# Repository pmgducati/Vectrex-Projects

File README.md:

# Vectrex-Projects
I created a few things for my Vectrex:

I have included the Gerber files for the PCBs in the controller and STLs of all the 3D printed parts. (the Eagle PCBs and Solidworks CAD Models are also inlcuded). Feel free to use my designs for yourself and modifiy them as you see fit.  

The designs are for personal use and may not be used for commericial use.

  1. A analog controller with a x-Axis sterring wheel, exposed center adjustment, headphone jack for foot pedal controls and a toggle to change what button the footpedal triggers.

  2. A bezel to work with Blacklighter's UV reactive overalys

  3. A shell for Vectrexer's VecMulti Cart

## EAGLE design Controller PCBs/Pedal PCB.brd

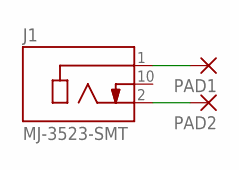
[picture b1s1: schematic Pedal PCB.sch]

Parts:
J1: MJ-3523-SMT; CUI_MJ-3523-SMT
PAD1, PAD2: SMD2; SMD1,27-2,54

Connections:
unnamed: J1.1, PAD1.1
unnamed: J1.2, PAD2.1

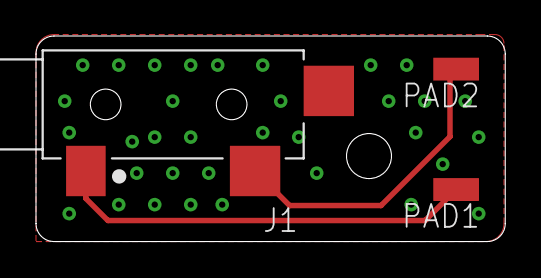
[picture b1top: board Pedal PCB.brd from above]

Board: 2 copper layers, 26.1 x 11.4 mm, 3 parts (0 on the bottom side), 2 nets.

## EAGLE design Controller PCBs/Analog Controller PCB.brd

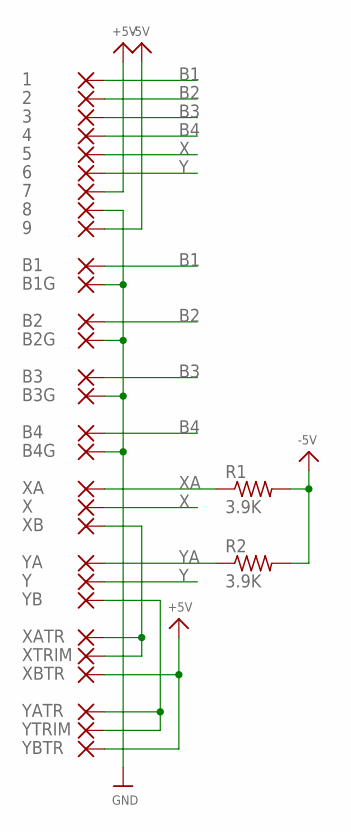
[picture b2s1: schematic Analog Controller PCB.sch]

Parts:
1, 2, 3, 4, 5, 6, 7, 8, 9: SMD2; SMD1,27-2,54
B1, B1G, B2, B2G, B3, B3G, B4, B4G: SMD2; SMD1,27-2,54
R1, R2: 3.9K; R1206
X: SMD2; SMD1,27-2,54
XA: SMD2; SMD1,27-2,54
XATR: SMD2; SMD1,27-2,54
XB: SMD2; SMD1,27-2,54
XBTR: SMD2; SMD1,27-2,54
XTRIM: SMD2; SMD1,27-2,54
Y: SMD2; SMD1,27-2,54
YA: SMD2; SMD1,27-2,54
YATR: SMD2; SMD1,27-2,54
YB: SMD2; SMD1,27-2,54
YBTR: SMD2; SMD1,27-2,54
YTRIM: SMD2; SMD1,27-2,54

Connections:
+5V: 7.1, XBTR.1, YBTR.1
-5V: 9.1, R1.2, R2.2
B1: 1.1, B1.1
B2: 2.1, B2.1
B3: 3.1, B3.1
B4: 4.1, B4.1
GND: 8.1, B1G.1, B2G.1, B3G.1, B4G.1
X: 5.1, X.1
XA: R1.1, XA.1
XB: XATR.1, XB.1, XTRIM.1
Y: 6.1, Y.1
YA: R2.1, YA.1
YB: YATR.1, YB.1, YTRIM.1

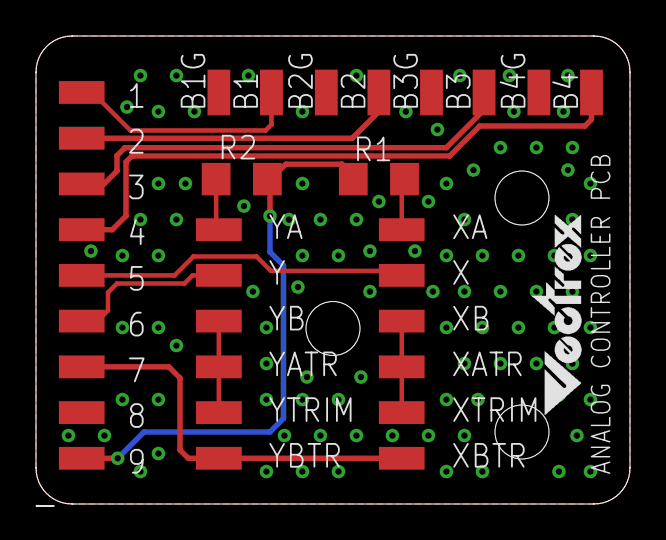
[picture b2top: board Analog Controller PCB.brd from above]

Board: 2 copper layers, 33.0 x 26.0 mm, 31 parts (0 on the bottom side), 13 nets.

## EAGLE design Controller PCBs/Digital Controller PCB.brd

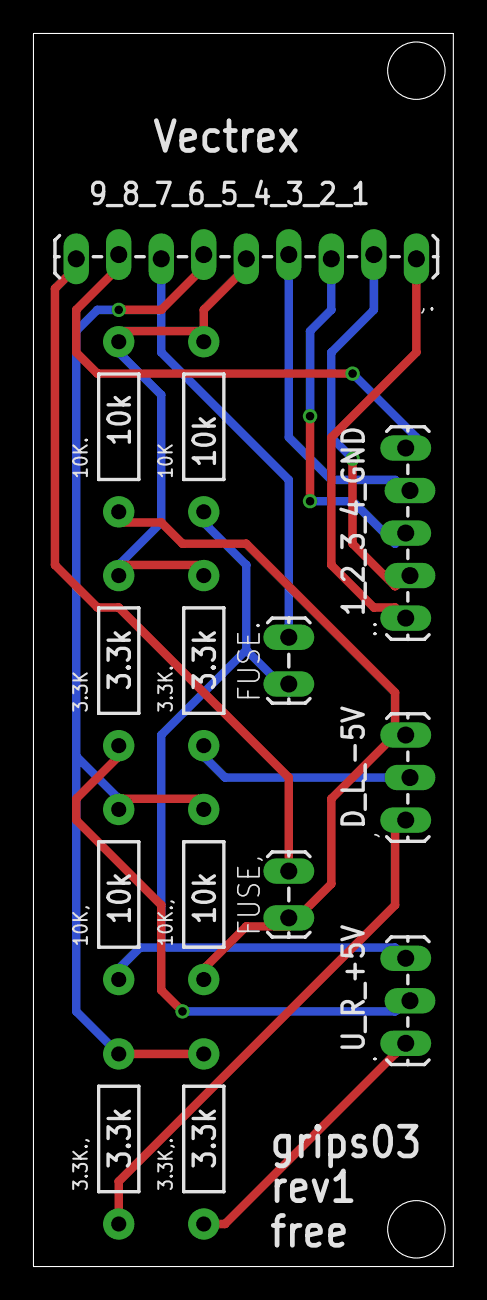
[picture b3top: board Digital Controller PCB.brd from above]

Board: 2 copper layers, 25.1 x 73.7 mm, 14 parts (0 on the bottom side), 15 nets.

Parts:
3.3K, 3.3K,., 3.3K., 3.3K.,, 10K, 10K,, 10K., 10K.,: AXIAL-0.4
,: 1X03_LOCK_LONGPADS
,.: M09LOCK-LONGPADS; 1X09_LOCK_LONGPADS
.: 1X03_LOCK_LONGPADS
..: 1X05_LOCK_LONGPADS
FUSE,: M02LOCK_LONGPADS; 1X02_LOCK_LONGPADS
FUSE.: M02LOCK_LONGPADS; 1X02_LOCK_LONGPADS

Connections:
+5V: 10K.P$1, 10K,.P$1, ..3, FUSE..1
+5V(7): ,..7, FUSE..2
-5V: 10K..P$1, 10K.,.P$1, ,.3, FUSE,.1
-5V(9): ,..9, FUSE,.2
B1: ,..1, ...1
B2: ,..2, ...2
B3: ,..3, ...3
B4: ,..4, ...4
DOWN: 3.3K.,.P$1, ,.1
GND: ,..8, ...5
HPOT: 3.3K.P$2, 3.3K..P$2, 10K.P$2, 10K..P$2, ,..5
LEFT: 3.3K..P$1, ,.2
RIGHT: 3.3K.P$1, ..2
UP: 3.3K,..P$1, ..1
VPOT: 3.3K,..P$2, 3.3K.,.P$2, 10K,.P$2, 10K.,.P$2, ,..6

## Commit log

2023-11-03 VecMulti Shell CAD
    Adding custom shell that I created as I dont like to 3D printed box it came in
2023-11-16 Steering Controller, UV Bezel Progress
    The UV Bezel is ready for the first print, I am waiting on the Rotary Switch so I can finished the CAD for the Controller Shell
2023-11-28 Sort Update
    Working through the sort function, uploading for review
2023-12-11 Part Updates
    UV Bezel - The cutout for the switch has been made larger to accommodate the switch I changed over to.
    MultiCart - My height measurement was .51mm off resulting in a very snug fit with the cart. I reduced the height over by .51mm and added two more screw bosses in the corners of the cart to help with 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
    Steering Controller - Modified housing to fit an alternate potentiometer.
2023-12-15 SD Card Slot Update
    Adjusted the height and size of SD Card Slot

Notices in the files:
parts and their libraries:
microbuilder: This work is placed in the public domain, and may be freely used for commercial and non-commercial work with the following conditions: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
SparkFun-Connectors: Licensing: CC v3.0 Share-Alike You are welcome to use this library for commercial purposes.
